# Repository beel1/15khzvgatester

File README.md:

# 15khzvgatester

It's free.

Based on Nick Gammons work: http://www.gammon.com.au/forum/?id=11608

# DTCTR notes

Make sure your vias are covered othervise you'll probably connect them to the battery's GND.

# Multisync software notes

Keep switch pressed for ~10 seconds to change video mode

# Rev2 of Arduino Uno shield

Allows a mini logic analyzer to be plugged in J3

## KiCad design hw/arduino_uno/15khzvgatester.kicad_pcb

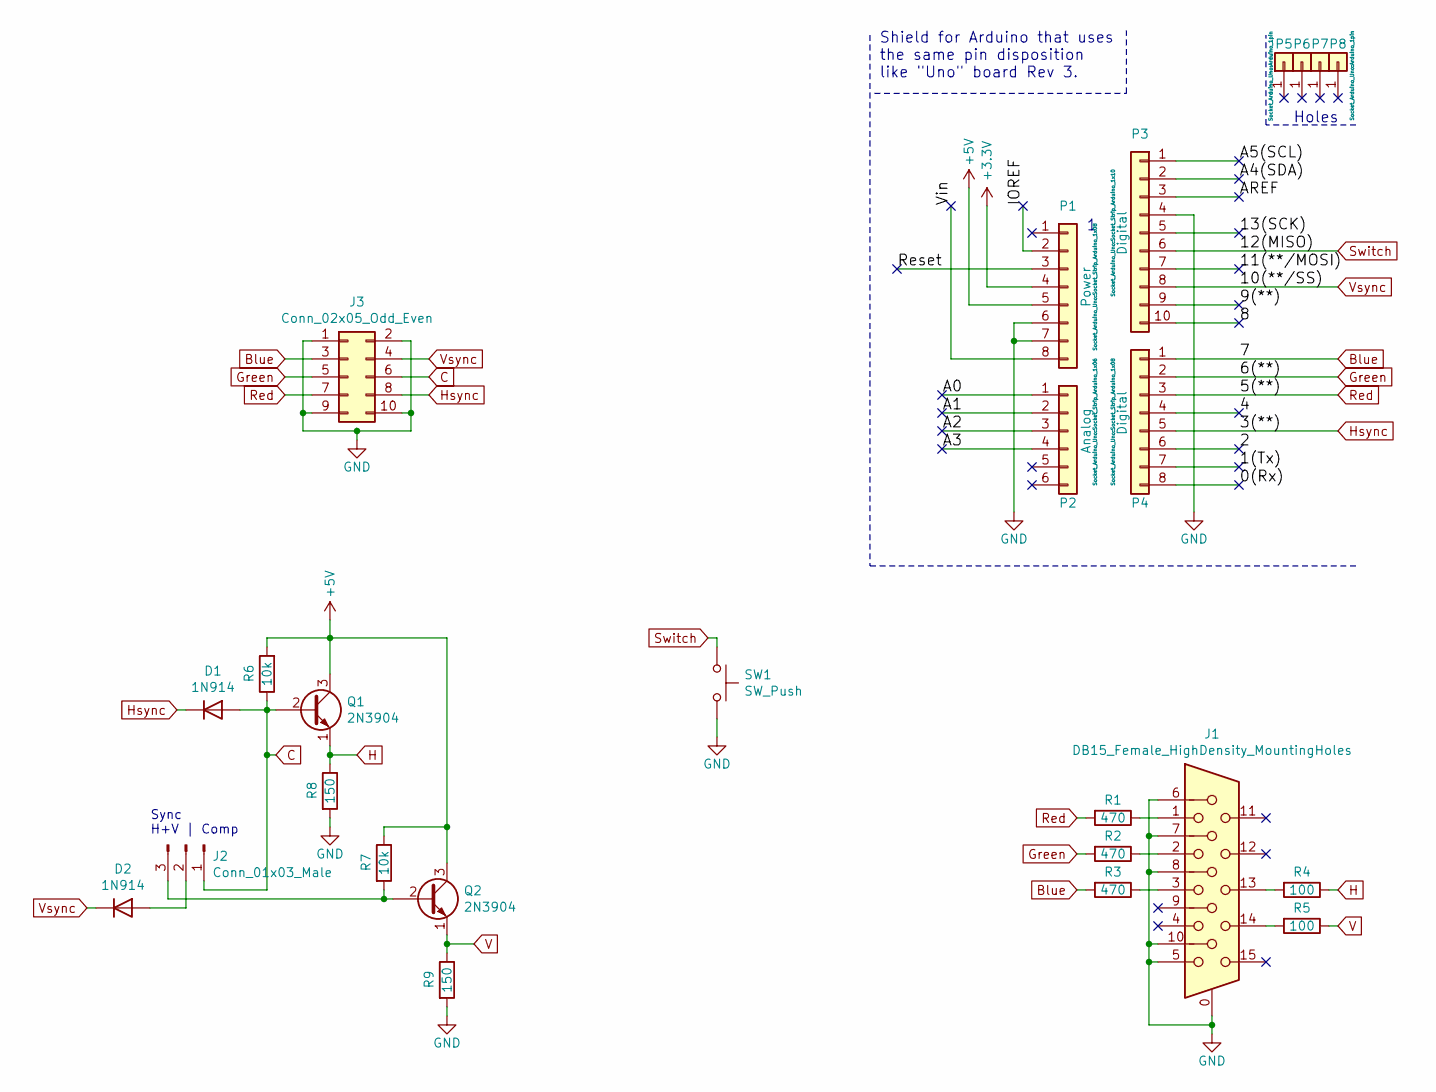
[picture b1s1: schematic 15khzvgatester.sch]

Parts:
D1, D2: 1N914; D_DO-35_SOD27_P7.62mm_Horizontal
J1: DB15_Female_HighDensity_MountingHoles; DSUB-15-HD_Female_Horizontal_P2.29x1.98mm_EdgePinOffset8.35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
J2: Conn_01x03_Male; Pin_Header_Straight_1x03_Pitch2.54mm
J3: Conn_02x05_Odd_Even; Socket_Strip_Straight_2x05_Pitch2.54mm
P1: Power; Socket_Strip_Arduino_1x08
P2: Analog; Socket_Strip_Arduino_1x06
P3: Digital; Socket_Strip_Arduino_1x10
P4: Digital; Socket_Strip_Arduino_1x08
P5, P6, P7, P8: CONN_01X01; Arduino_1pin
Q1, Q2: 2N3904; TO-92_Inline_Wide
R1, R2, R3: 470; Resistor_SMD+THTuniversal_0805to1206_RM10_HandSoldering_Rev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
R4, R5: 100; Resistor_SMD+THTuniversal_0805to1206_RM10_HandSoldering_Rev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
R6, R7: 10k; Resistor_SMD+THTuniversal_0805to1206_RM10_HandSoldering_Rev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
R8, R9: 150; Resistor_SMD+THTuniversal_0805to1206_RM10_HandSoldering_Rev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
SW1: SW_Push; SW_Tactile_Straight_KSA0Axx1LFTR

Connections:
+3V3: P1.4
+5V: P1.5, Q1.3 (C), Q2.3 (C), R6.2, R7.1
/0(Rx): P4.8
/1(Tx): P4.7
/2: P4.6
/4: P4.4
/8: P3.10
/9(**): P3.9
/11(**/MOSI): P3.7
/13(SCK): P3.5
/A0: P2.1
/A1: P2.2
/A2: P2.3
/A3: P2.4
/A4(SDA): P3.2
/A5(SCL): P3.1
/AREF: P3.3
/IOREF: P1.2
/Reset: P1.3
/Vin: P1.8
Blue: J3.3, P4.1, R3.2
C: D1.2 (A), J2.1, J3.6, Q1.2 (B), R6.1
GND: J1.0, J1.5, J1.6, J1.7, J1.8, J1.10, J3.1, J3.2, J3.9, J3.10, P1.6, P1.7, P3.4, R8.2, R9.2, SW1.2
Green: J3.5, P4.2, R2.2
H: Q1.1 (E), R4.1, R8.1
Hsync: D1.1 (K), J3.8, P4.5
unnamed: D2.2 (A), J2.2
unnamed: J1.1, R1.1
unnamed: J1.2, R2.1
unnamed: J1.3, R3.1
unnamed: J1.13, R4.2
unnamed: J1.14, R5.2
unnamed: J2.3, Q2.2 (B), R7.2
Red: J3.7, P4.3, R1.2
Switch: P3.6, SW1.1
V: Q2.1 (E), R5.1, R9.1
Vsync: D2.1 (K), J3.4, P3.8

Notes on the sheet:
Holes
Shield for Arduino that uses the same pin disposition like "Uno" board Rev 3.
Sync H+V | Comp

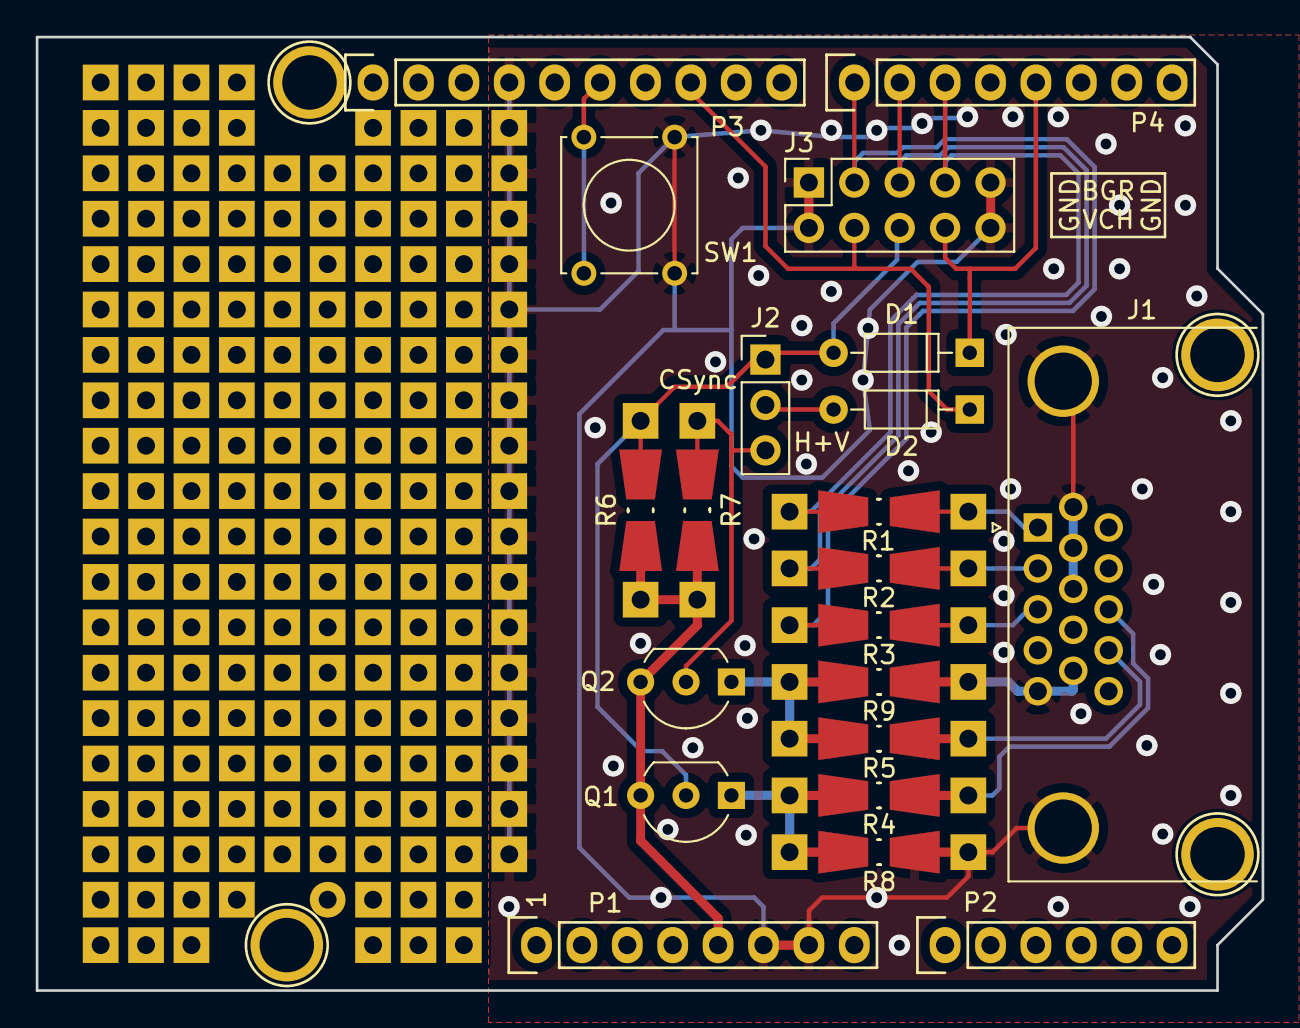
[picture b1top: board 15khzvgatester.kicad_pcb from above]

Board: 2 copper layers, 68.6 x 53.3 mm, 25 parts (0 on the bottom side), 18 nets.

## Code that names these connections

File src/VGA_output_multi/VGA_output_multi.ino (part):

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#include <avr/sleep.h>
#include "screenFontST.h"

const byte hSyncPin = 3; // <------- HSYNC

const byte redPin   = 5; // <------- Red pixel data
const byte greenPin = 6; // <------- Green pixel data
const byte bluePin  = 7; // <------- Blue pixel data

const byte vSyncPin = 10; // <------- VSYNC

const byte switchPin = 12; // <------- Switch input

/* Length of displayed mode name without null-terminator */
#define STRING_LEN 5u
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// Timer 1 - Vertical sync
// Lower priority than Timer 2

// output    OC1B   pin 16  (D10) <------- VSYNC

//   Period: 16.64 mS (60 Hz)
//      1/60 * 1e6 = 16666.66 uS
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// Timer 2 - Horizontal sync
// Higher priority than Timer 1

// output    OC2B   pin 5  (D3)   <------- HSYNC

//   Period: 32 uS (31.25 kHz)
//      (1/60) / 525 * 1e6 = 31.74 uS
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
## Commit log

2023-11-11 Add remake of Arduino Uno shield
    With switch, configurable Sync output, logic analyzer header and prototype area. Made with KiCad 5.1.6.
2023-11-22 Add BOM
2023-12-03 Add multisync software with VGA and 3 Atari ST video modes
    Every 10 seconds the button is read, if not pressed the top right "pixel" color changes otherwise the video mode is changed.
    Video modes defined are VGA (similar to original software), Atari ST High 71Hz, Atari ST Low 60Hz and Atari ST Low 50Hz based on measures made on my PAL STE.
    Current video mode name is displayed on screen.
2023-12-03 Add pictures of what multisync version outputs
2023-12-03 Update README.md
    Embed pictures of video output
2023-12-03 Add picture of /hw/arduino_uno board
    With a logic analyzer than can be plugged directly in J3 (unpopulated here)
2023-12-03 Update README.md
    Embed picture of \hw\arduino_uno board
